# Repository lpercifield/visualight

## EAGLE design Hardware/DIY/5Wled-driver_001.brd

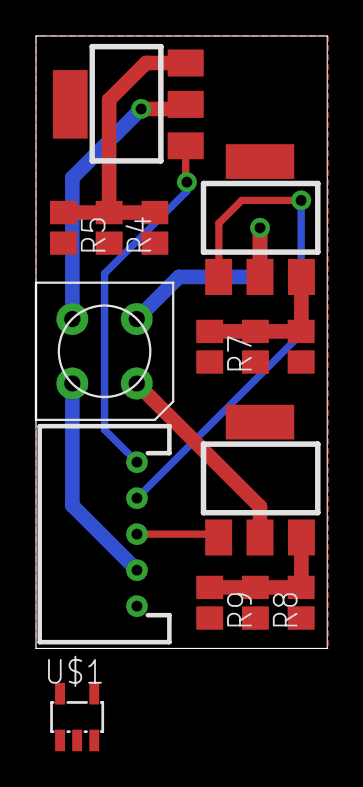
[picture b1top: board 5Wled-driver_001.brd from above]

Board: 2 copper layers, 16.2 x 34.0 mm, 15 parts (0 on the bottom side), 11 nets.

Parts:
LED1: RGBLED_CA4.5MM; 5WRGBLED
PL1: DF3R-05
Q1, Q2, Q3: IRLL024; SOT-223
R1, R2, R3, R4, R5, R6, R7, R8, R9: R2012
U$1: TPS61040DBV; SOT23-5L

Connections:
BLUE: PL1.1, Q1.1
GND: PL1.5, R1.2, R2.2, R3.2, R4.2, R5.2, R6.2, R7.2, R8.2, R9.2, U$1.2
GREEN: PL1.2, Q3.1
unnamed: LED1.3, Q1.2
unnamed: LED1.1, Q2.2
unnamed: LED1.2, Q3.2
unnamed: Q1.3, R1.1, R4.1, R5.1
unnamed: Q3.3, R2.1, R6.1, R7.1
unnamed: Q2.3, R3.1, R8.1, R9.1
RED: PL1.3, Q2.1
VCC: LED1.4, PL1.4

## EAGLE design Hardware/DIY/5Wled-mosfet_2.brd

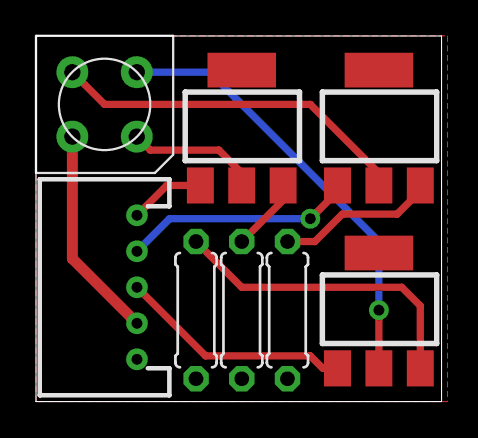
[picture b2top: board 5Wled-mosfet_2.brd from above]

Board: 2 copper layers, 22.5 x 20.3 mm, 8 parts (0 on the bottom side), 11 nets.

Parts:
LED1: RGBLED_CA4.5MM; 5WRGBLED
PL1: DF3R-05
Q1, Q2, Q3: IRLL024; SOT-223
R1, R2, R3: 0207/7

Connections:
BLUE: PL1.1, Q1.1
GND: PL1.5, R1.2, R2.2, R3.2
GREEN: PL1.2, Q3.1
unnamed: LED1.1, Q1.2
unnamed: LED1.3, Q3.2
unnamed: LED1.2, Q2.2
unnamed: Q1.3, R1.1
unnamed: Q3.3, R2.1
unnamed: Q2.3, R3.1
RED: PL1.3, Q2.1
VCC: LED1.4, PL1.4

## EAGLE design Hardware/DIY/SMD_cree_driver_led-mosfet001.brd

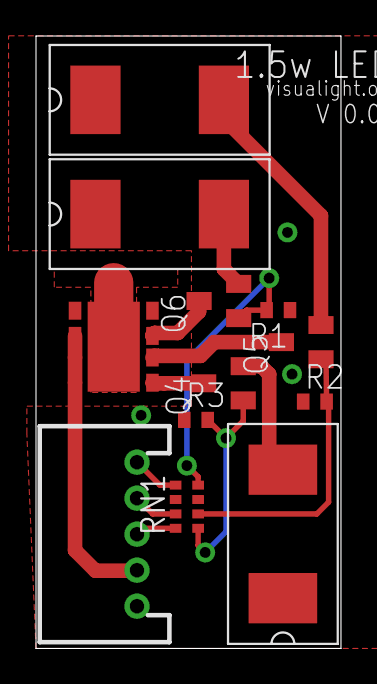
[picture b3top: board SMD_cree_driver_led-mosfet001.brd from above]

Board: 2 copper layers, 16.9 x 34.0 mm, 12 parts (0 on the bottom side), 14 nets.

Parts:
PL1: DF3R-05
Q4, Q5, Q6: BSS123; SOT23
R1, R2, R3: 100k; R0402
RN1: 2.2k; 0603-ARC
U$1: CREE_XLAMP_RGBW; CREE_XLAMP_XML
U$2, U$3, U$4: NSI50350AST3G; SMC-2

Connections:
BLUE: Q4.1, R3.2, RN1.5
BLUE_OUT: PL1.3, RN1.4
GND: PL1.5, R1.1, R2.1, R3.1, U$2.C, U$3.C, U$4.C
GREEN: Q6.1, R1.2, RN1.8
GREEN_OUT: PL1.1, RN1.1
unnamed: Q6.3, U$1.6
unnamed: Q5.3, U$1.7
unnamed: Q4.3, U$1.8
unnamed: Q6.2, U$2.A
unnamed: Q4.2, U$4.A
unnamed: Q5.2, U$3.A
RED: Q5.1, R2.2, RN1.6
RED_OUT: PL1.2, RN1.3
VCC: PL1.4, U$1.1, U$1.2, U$1.3

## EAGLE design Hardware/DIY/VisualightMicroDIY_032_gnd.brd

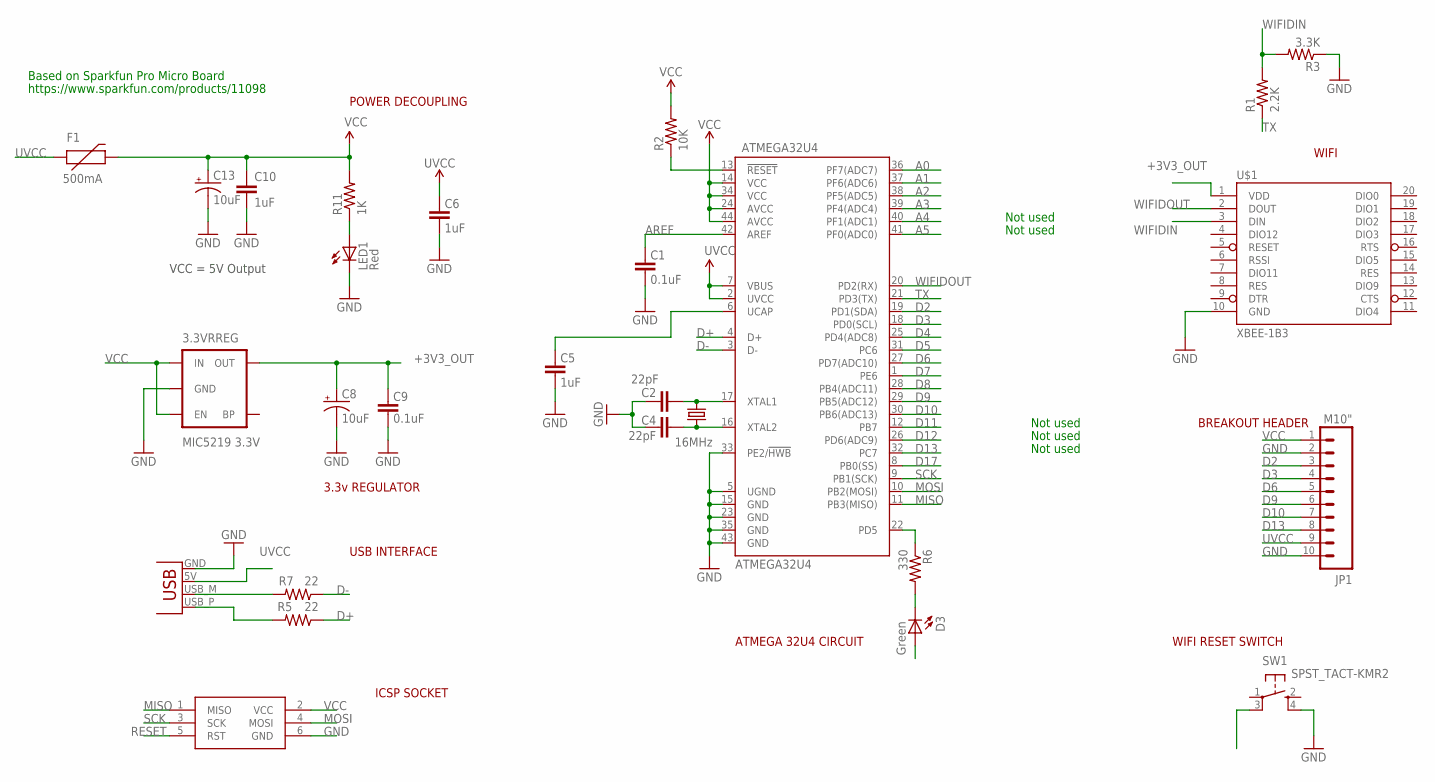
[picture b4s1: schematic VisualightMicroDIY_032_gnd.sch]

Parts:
3.3VRREG: MIC5219 3.3V; SOT23-5
ATMEGA32U4: ATMEGA32U4; SPARKFUN-DIGITALIC_TQFP44
C1, C9: 0.1uF; 0402-CAP
C2, C4: 22pF; 0402-CAP
C5, C6, C10: 1uF; 0402-CAP
C8, C13: 10uF; EIA3216
D3: Green; LED-0603
F1: 500mA; PTC-1206
ISP1: AVRISP-6; AVRISP
JP1: M10"; 1X10
LED1: Red; LED-0603
R1: 2.2K; 0402-RES
R2: 10K; 0402-RES
R3: 3.3K; 0402-RES
R5, R7: 22; 0402-RES
R6: 330; 0402-RES
R11: 1K; 0402-RES
SW1: SPST_TACT-KMR2; KMR2
U$1: XBEE-1B3; XBEE-SMD
X2: USBPCB; USB-A-PCB
Y1: 16MHz; CRYSTAL-SMD-5X3

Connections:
+3V3_OUT: 3.3VRREG.5 (OUT), C8.A (+), C9.2, U$1.1 (VDD)
A0: ATMEGA32U4.36 (PF7(ADC7))
A1: ATMEGA32U4.37 (PF6(ADC6))
A2: ATMEGA32U4.38 (PF5(ADC5))
A3: ATMEGA32U4.39 (PF4(ADC4))
A4: ATMEGA32U4.40 (PF1(ADC1))
A5: ATMEGA32U4.41 (PF0(ADC0))
AREF: ATMEGA32U4.42 (AREF), C1.2
D2: ATMEGA32U4.19 (PD1(SDA)), JP1.3
D3: ATMEGA32U4.18 (PD0(SCL)), JP1.4
D4: ATMEGA32U4.25 (PD4(ADC8))
D5: ATMEGA32U4.31 (PC6)
D6: ATMEGA32U4.27 (PD7(ADC10)), JP1.5
D7: ATMEGA32U4.1 (PE6), SW1.3 (P1)
D8: ATMEGA32U4.28 (PB4(ADC11))
D9: ATMEGA32U4.29 (PB5(ADC12)), JP1.6
D10: ATMEGA32U4.30 (PB6(ADC13)), JP1.7
D11: ATMEGA32U4.12 (PB7)
D12: ATMEGA32U4.26 (PD6(ADC9))
D13: ATMEGA32U4.32 (PC7), JP1.8
D17: ATMEGA32U4.8 (PB0(SS))
D+: ATMEGA32U4.4 (D+), R5.1
D-: ATMEGA32U4.3 (D-), R7.1
GND: 3.3VRREG.2 (GND), ATMEGA32U4.5 (UGND), ATMEGA32U4.15 (GND), ATMEGA32U4.23 (GND), ATMEGA32U4.33 (PE2/!HWB), ATMEGA32U4.35 (GND), ATMEGA32U4.43 (GND), C1.1, C2.2, C4.2, C5.1, C6.1, C8.C (-), C9.1, C10.2, C13.C (-), ISP1.6 (GND), JP1.2, JP1.10, LED1.C, R3.1, SW1.4 (S1), U$1.10 (GND), X2.GND
MISO: ATMEGA32U4.11 (PB3(MISO)), ISP1.1 (MISO)
MOSI: ATMEGA32U4.10 (PB2(MOSI)), ISP1.4 (MOSI)
unnamed: ATMEGA32U4.16 (XTAL2), C4.1, Y1.1
unnamed: ATMEGA32U4.17 (XTAL1), C2.1, Y1.3 (2)
unnamed: ATMEGA32U4.6 (UCAP), C5.2
unnamed: R7.2, X2.USB_M (D-)
unnamed: D3.C, R6.2
unnamed: R5.2, X2.USB_P (D+)
unnamed: LED1.A, R11.1
RESET: ATMEGA32U4.13 (!RESET), ISP1.5 (RST), R2.1
SCK: ATMEGA32U4.9 (PB1(SCK)), ISP1.3 (SCK)
TX: ATMEGA32U4.21 (PD3(TX)), R1.1
TXLED: ATMEGA32U4.22 (PD5), R6.1
UVCC: ATMEGA32U4.2 (UVCC), ATMEGA32U4.7 (VBUS), C6.2, F1.1, JP1.9, X2.5V (VBUS)
VCC: 3.3VRREG.1 (IN), 3.3VRREG.3 (EN), ATMEGA32U4.14 (VCC), ATMEGA32U4.24 (AVCC), ATMEGA32U4.34 (VCC), ATMEGA32U4.44 (AVCC), C10.1, C13.A (+), D3.A, F1.2, ISP1.2 (VCC), JP1.1, R2.2, R11.2
WIFIDIN: R1.2, R3.2, U$1.3 (DIN)
WIFIDOUT: ATMEGA32U4.20 (PD2(RX)), U$1.2 (DOUT)

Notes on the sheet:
VCC = 5V Output
Not used
Based on Sparkfun Pro Micro Board
https://www.sparkfun.com/products/11098
USB INTERFACE
ICSP SOCKET
3.3v REGULATOR
POWER DECOUPLING
ATMEGA 32U4 CIRCUIT
WIFI RESET SWITCH
BREAKOUT HEADER
WIFI

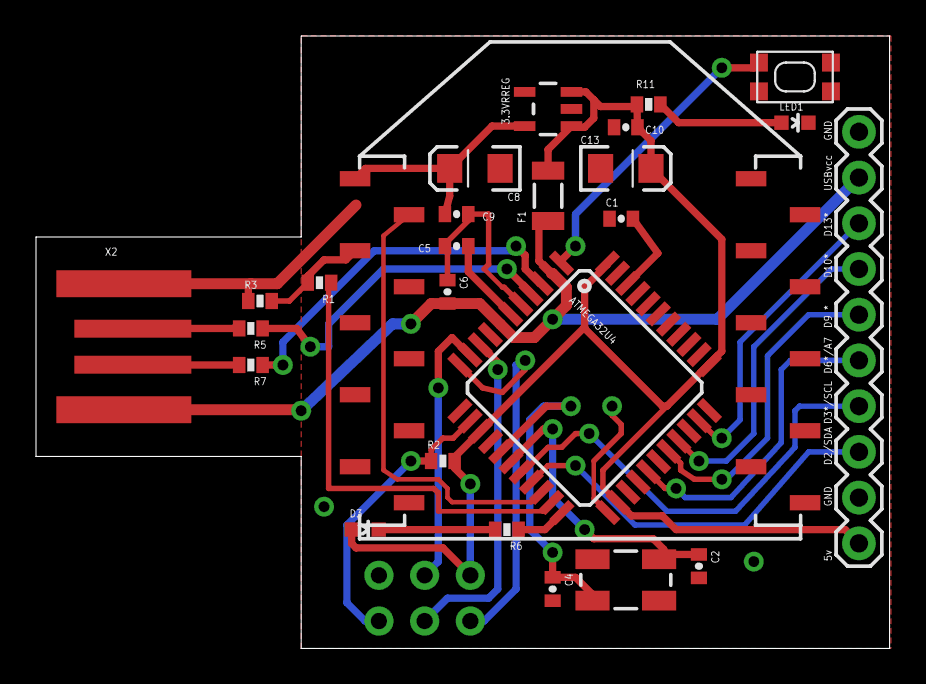
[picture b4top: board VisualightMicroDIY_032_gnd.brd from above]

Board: 2 copper layers, 47.4 x 34.0 mm, 27 parts (1 on the bottom side), 29 nets.

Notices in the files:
parts and their libraries:
SparkFun-DigitalIC: Licensing: CC v3.0 Share-Alike You are welcome to use this library for commercial purposes.
